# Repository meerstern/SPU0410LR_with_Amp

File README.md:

# SPU0410LR_with_Amp
The Converter board of Kicad Data for SPU0410LR with Apmlifer

## 概要
約50倍の増幅回路[TLV316][0]とKnowles社製[アナログ出力MEMSマイクSPU0410LR5H][1]を搭載した2.54mmピッチ変換基板です。  
可聴音から超音波(100Hz～80kHz)までの幅広い帯域を高感度にセンシングすることが可能です。  
超音波センサや超音波通信などに使用可能です。  
約50倍のアンプ回路を搭載することでArduinoといったマイコンのアナログ入力に直接接続できます。  
マイク穴は基板裏面の丸印部分です。  
電源電圧1.8V~3.6V

## 超音波マイク比較
 用途に応じて様々な製品をラインアップしています  
| 製品名 | インタフェース | アンプ搭載有無 | 用途 | 
|:-----------|:------------|:------------|:------------|
| [アナログ出力マイク][A] | アナログ | 無 | 任意のアンプ回路を使用したい場合 | 
| [可変アンプ内蔵アナログ出力マイク][B] | アナログ | 有(可変1~50倍) | 増幅率の調整が必要な場合 |	
| [アンプ内蔵アナログ出力マイク(本製品)][C] |	アナログ | 有(固定50倍) | 一定した増幅が必要な場合	| 
| [デジタル出力マイク][D] |	デジタルPDM | 不要 | フルデジタルで実装する場合やワイドレンジが必要な場合 | 

## 販売サイト
  * [スイッチサイエンス][2]

## 告知
SPU0410LR5Hの生産完了に伴い、[後継品のSPV0142LR5H][5]に移行しました(26年4月)。

License - MIT

[1]: https://www.digikey.jp/product-detail/ja/knowles/SPU0410LR5H-QB-7/423-1139-1-ND/2420983 "*1"
[0]: http://www.tij.co.jp/product/jp/TLV316 "*0"
[2]: https://www.switch-science.com/products/5462

[A]: https://github.com/meerstern/SPU0410LR
[B]: https://github.com/meerstern/SPU0410LR_with_VariableAmp
[C]: https://github.com/meerstern/SPU0410LR_with_Amp
[D]: https://github.com/meerstern/SPH0641LU
[5]: https://github.com/meerstern/SPV0142LR5H_with_Amp

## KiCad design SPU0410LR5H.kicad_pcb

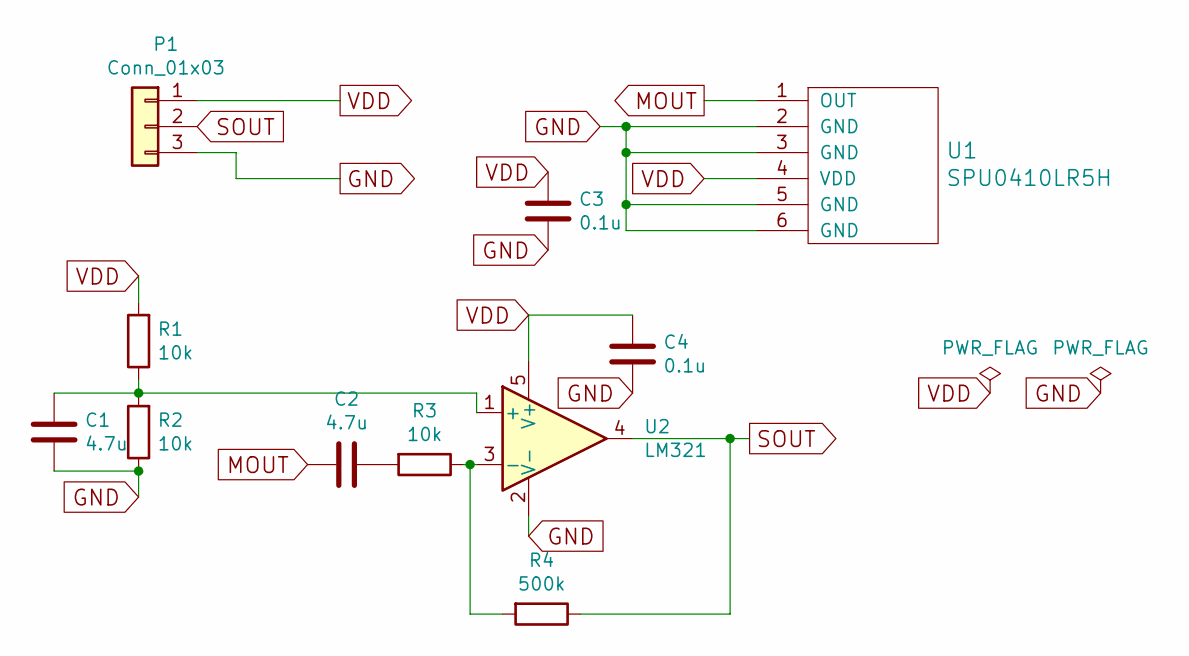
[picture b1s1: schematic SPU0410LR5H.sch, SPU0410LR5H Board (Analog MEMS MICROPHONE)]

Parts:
C1, C2: 4.7u; generic-SMD1608
C3: 0.1u; C-1206
C4: 0.1u; generic-SMD1608
P1: Conn_01x03; pinhead-1X03
R1, R2, R3: 10k; generic-SMD1608
R4: 500k; generic-SMD1608
U1: SPU0410LR5H
U2: LM321; SC-70-5

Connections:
GND: C1.2, C3.2, C4.2, P1.3, R2.1, U1.2 (GND), U1.3 (GND), U1.5 (GND), U1.6 (GND), U2.2 (V-)
MOUT: C2.2, U1.1 (OUT)
unnamed: C1.1, R1.1, R2.2, U2.1 (+)
unnamed: C2.1, R3.2
unnamed: R3.1, R4.2, U2.3 (-)
SOUT: P1.2, R4.1, U2.4
VDD: C3.1, C4.1, P1.1, R1.2, U1.4 (VDD), U2.5 (V+)

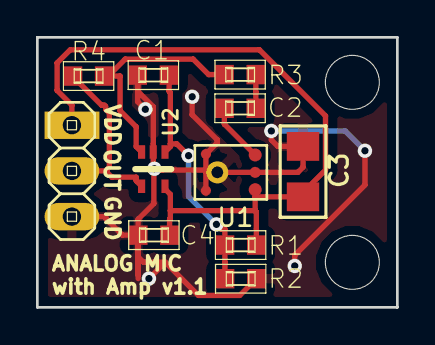
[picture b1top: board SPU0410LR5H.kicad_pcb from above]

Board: 2 copper layers, 20.0 x 15.0 mm, 13 parts (0 on the bottom side), 7 nets.

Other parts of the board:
REF1, REF2: MountingHole_3mm

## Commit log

2019-02-23 Add files
2019-02-23 Add README
2019-04-06 Add photos
2019-04-06 Add the pdf file of the circuit
2019-04-06 Update photo
2022-12-06 Add shop link
